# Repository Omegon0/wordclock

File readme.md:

# Quarter Past Five

This is a small 16x16 word clock that can tell the time with a minute resolution. It uses a Xiao RP2040 with four daisy-chained MAX7219 as the display with four key switches to set the time. Breakout pins for connecting a DS3231 RTC are included as well. Has a photoresistor for automatic light adjustment.

### Why?

Because reading the time in words gives me a sense of urgency that reading numbers does not. It makes me get things done more effectively. 

### Building instructions

Obtain parts labeled in the BOM. See either the table below. 

| Component     | Identifier     | Price    | Amazon link |
|---------------|----------------|----------|-------------|
| Xiao RP2040   | XIAO-RP2040    | $9.99    | [Amazon](https://www.amazon.com/Microcontroller-Dual-Core-MicroPython-CircuitPython-Interfaces/dp/B09NNVNW7M/)|
| DS3231        | RTC            | $12.99   | [Amazon](https://www.amazon.com/HiLetgo-AT24C32-Arduino-Without-Battery/dp/B00LX3V7F0/)|
| Switches      | switches       | $10.99*4 | [Amazon](https://www.amazon.com/Mciepny-Waterproof-Dustproof-Pre-Lubricated-Mechanical/dp/B0FF9MBBDR?th=1)|
| MAX7219       | led-matrix     | $8.28    | [Amazon](https://www.amazon.com/3PCS-MAX7219-Matrix-Display-Module/dp/B0FB99TY1Z/)|
| Photoresistor | photoresistor  | $7.39    | [Amazon](https://www.amazon.com/HiLetgo-Dependent-Photoresistor-Photoconductive-Resistance/dp/B00N1ZJUN4/)|
| CR2032        | N/A(separate)  | $3.97    | [Amazon](https://www.amazon.com/Amazon-Basics-CR2032-Compatible-Mercury-Free/dp/B0787K2XWZ/)|

Solder each component into the PCB accordingly, or follow the schematic to wire the pieces together. If using the PCB, make sure that things go the right direction. When soldering the MAX7219, solder the board with the LEDs first and then solder that to the PCB, not the other way around. It's a lot easier.

### Images

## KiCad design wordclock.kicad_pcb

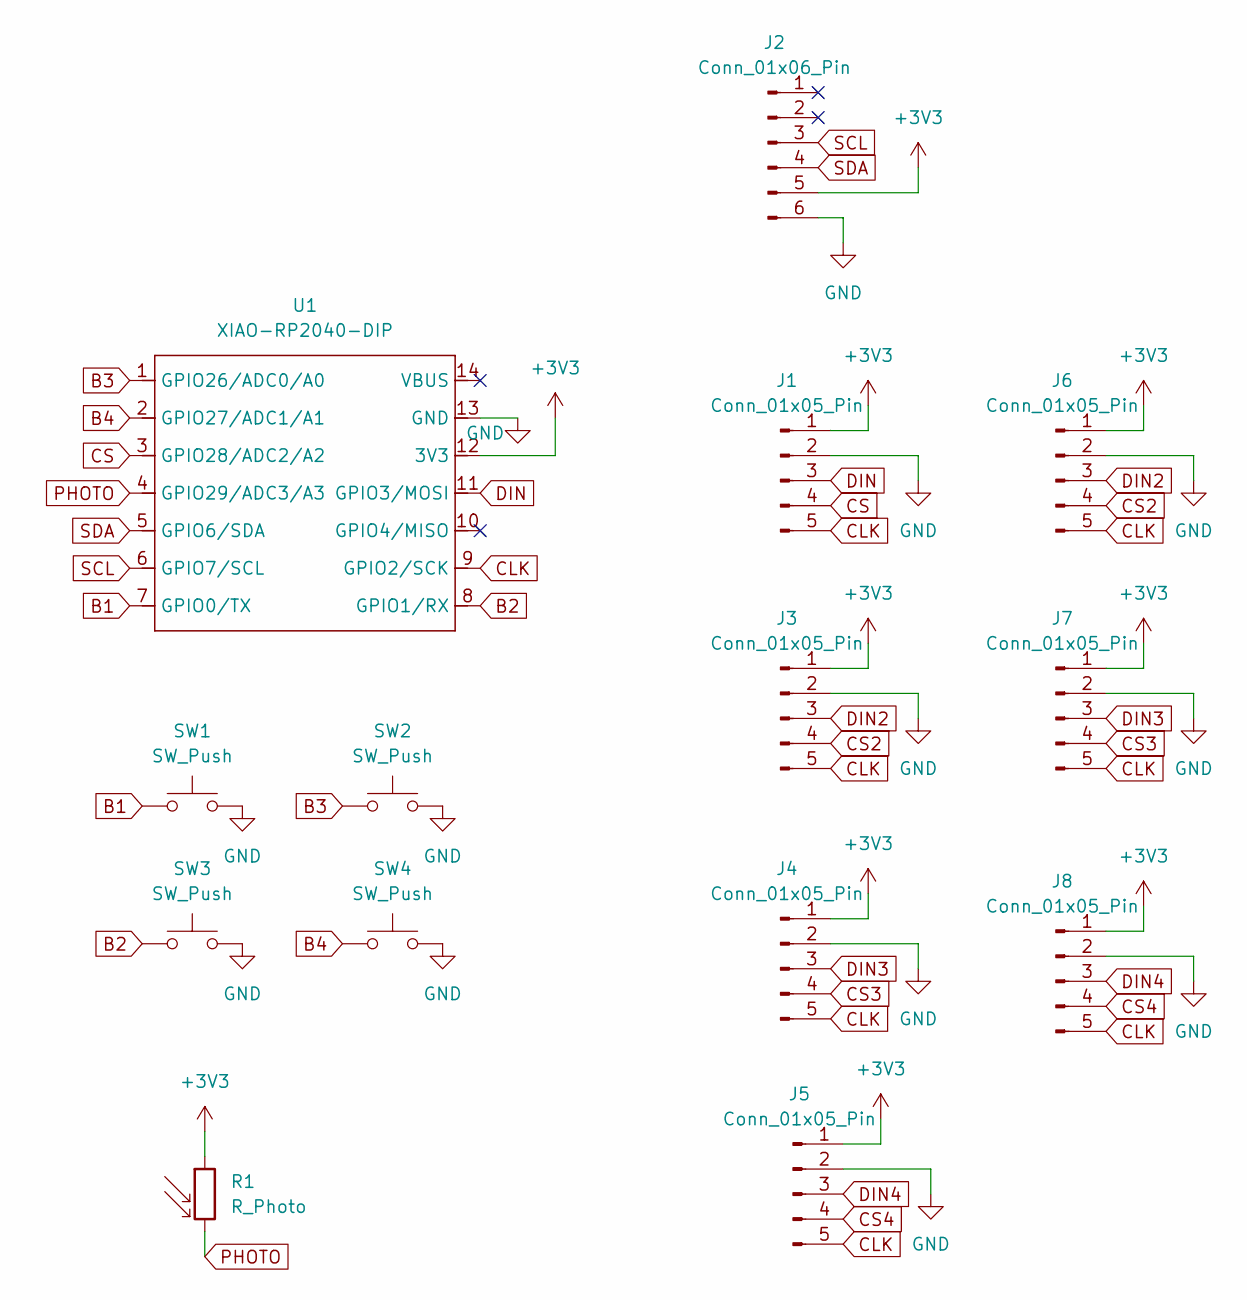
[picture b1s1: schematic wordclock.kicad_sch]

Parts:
J1, J3, J4, J5, J6, J7, J8: Conn_01x05_Pin; PinHeader_1x05_P2.54mm_Vertical
J2: Conn_01x06_Pin; PinHeader_1x06_P2.54mm_Vertical
R1: R_Photo; R_Axial_DIN0204_L3.6mm_D1.6mm_P1.90mm_Vertical
SW1, SW2, SW3, SW4: SW_Push; SW_Cherry_MX_1.00u_PCB
U1: XIAO-RP2040-DIP

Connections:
+3V3: J1.1, J2.5, J3.1, J4.1, J5.1, J6.1, J7.1, J8.1, R1.1, U1.12 (3V3)
B1: SW1.1, U1.7 (GPIO0/TX)
B2: SW3.1, U1.8 (GPIO1/RX)
B3: SW2.1, U1.1 (GPIO26/ADC0/A0)
B4: SW4.1, U1.2 (GPIO27/ADC1/A1)
CLK: J1.5, J3.5, J4.5, J5.5, J6.5, J7.5, J8.5, U1.9 (GPIO2/SCK)
CS: J1.4, U1.3 (GPIO28/ADC2/A2)
CS2: J3.4, J6.4
CS3: J4.4, J7.4
CS4: J5.4, J8.4
DIN: J1.3, U1.11 (GPIO3/MOSI)
DIN2: J3.3, J6.3
DIN3: J4.3, J7.3
DIN4: J5.3, J8.3
GND: J1.2, J2.6, J3.2, J4.2, J5.2, J6.2, J7.2, J8.2, SW1.2, SW2.2, SW3.2, SW4.2, U1.13 (GND)
PHOTO: R1.2, U1.4 (GPIO29/ADC3/A3)
SCL: J2.3, U1.6 (GPIO7/SCL)
SDA: J2.4, U1.5 (GPIO6/SDA)

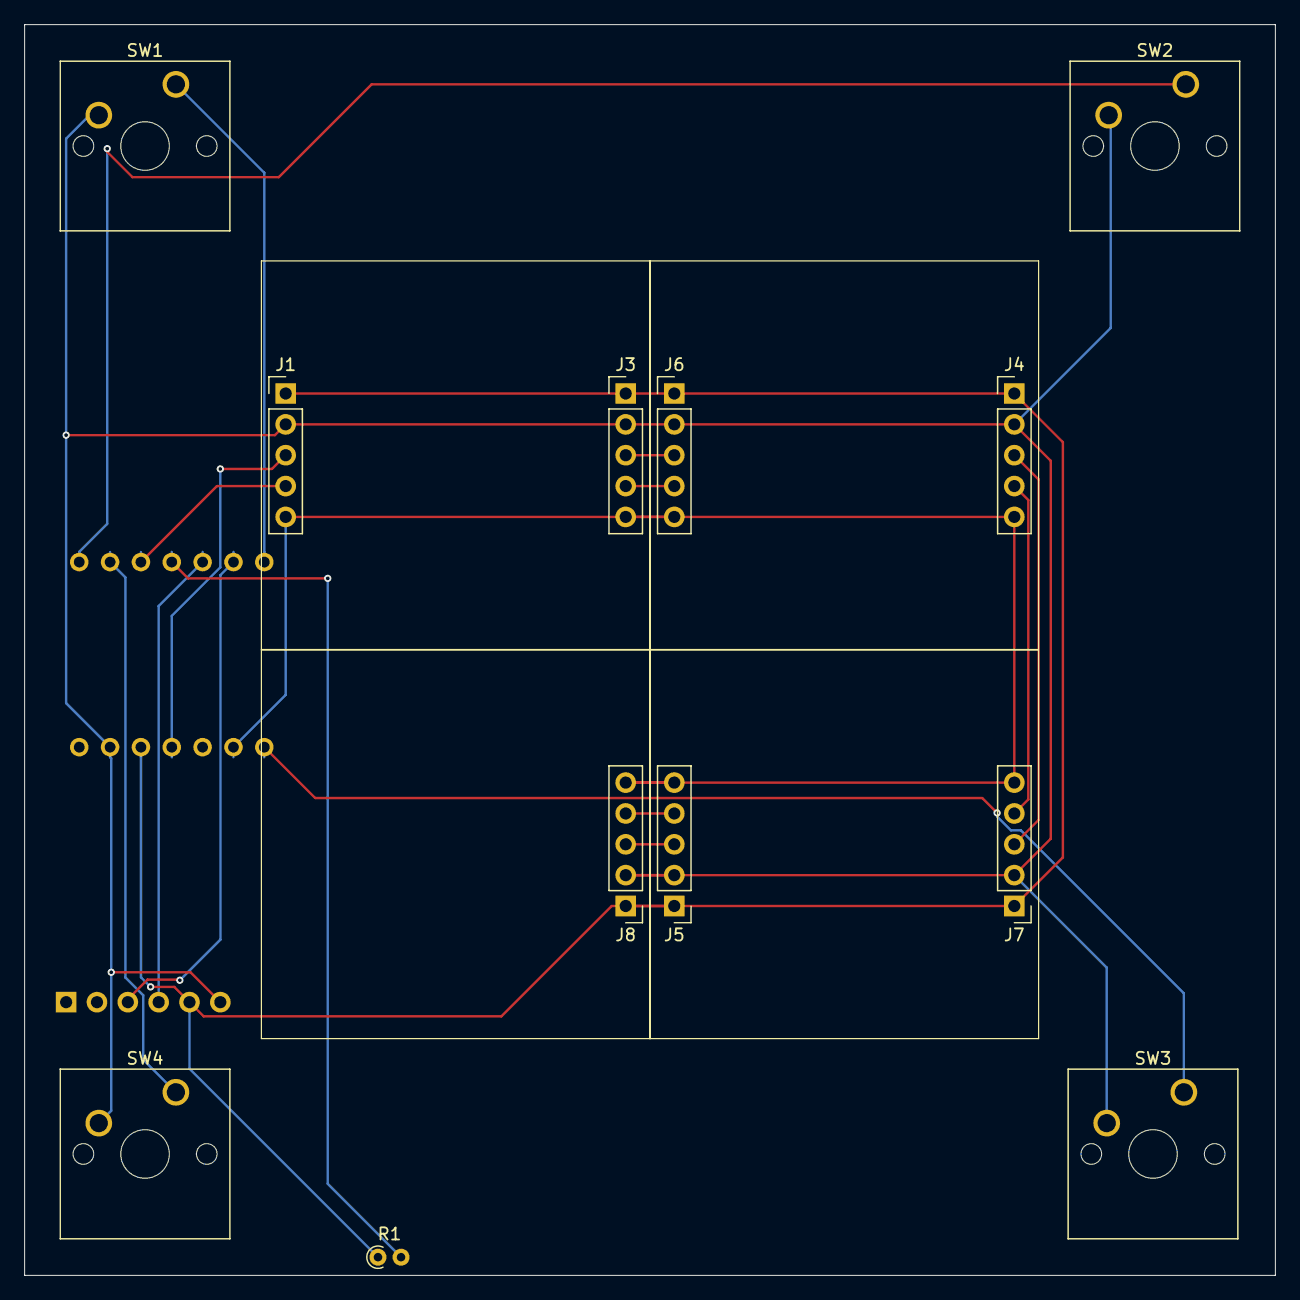
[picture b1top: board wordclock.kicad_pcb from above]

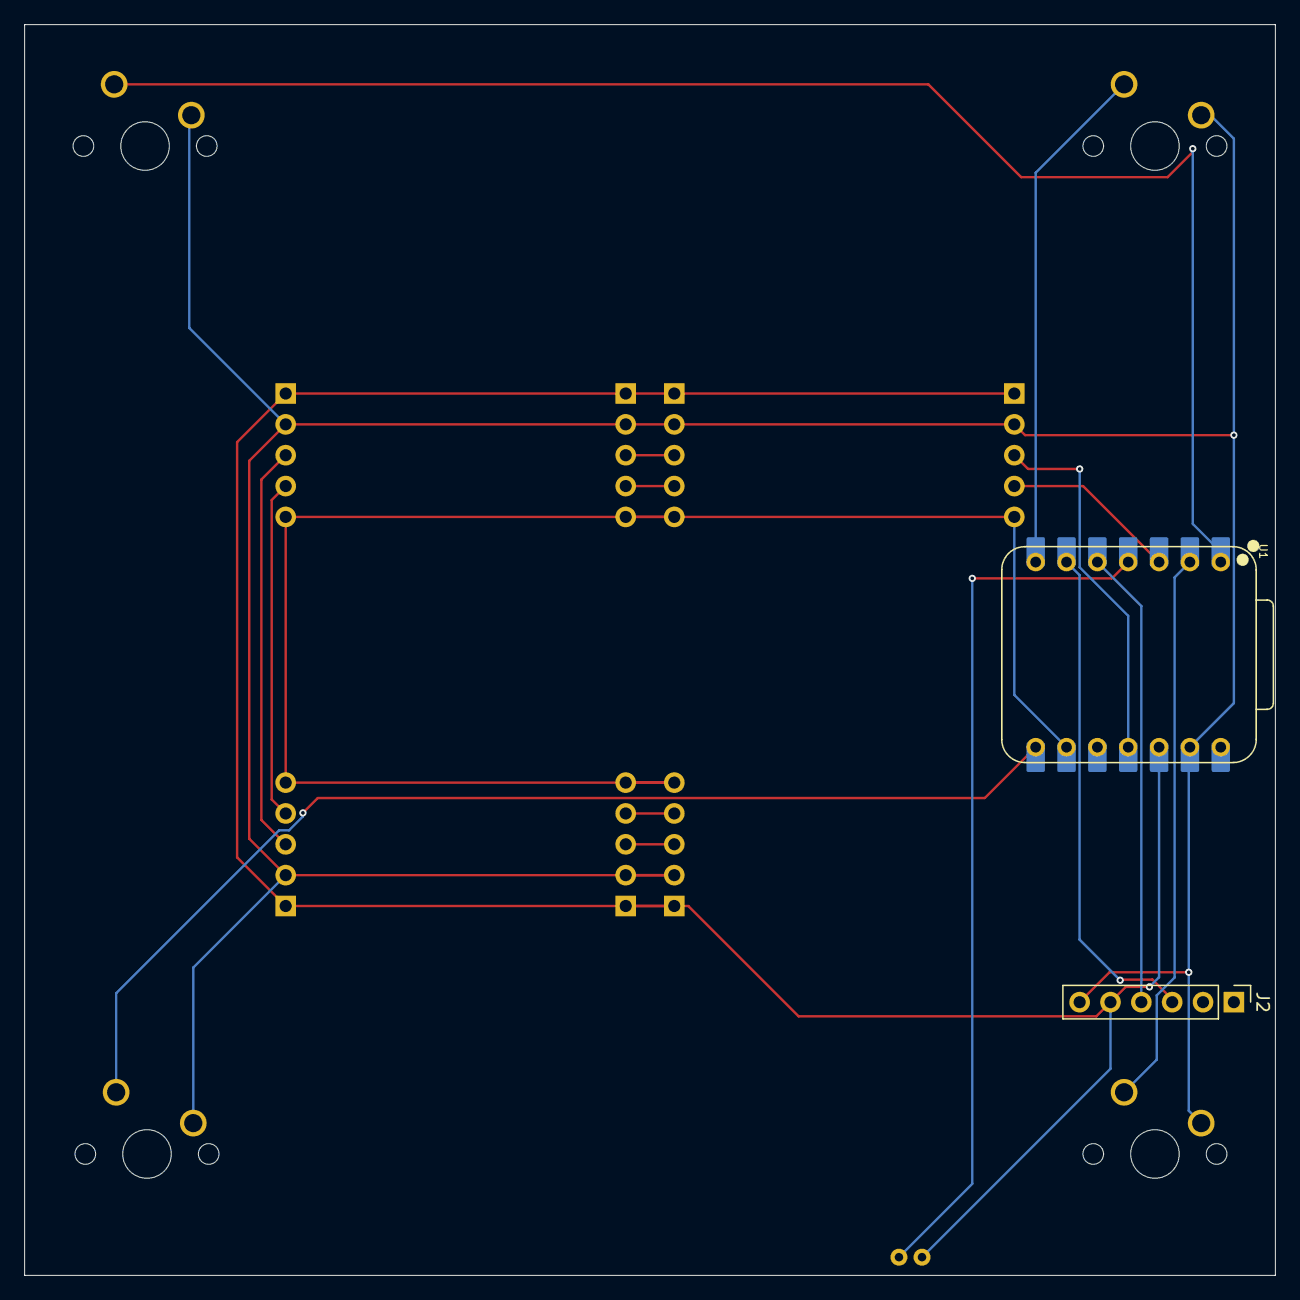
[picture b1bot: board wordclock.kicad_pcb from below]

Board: 2 copper layers, 103.0 x 103.0 mm, 14 parts (2 on the bottom side), 18 nets.

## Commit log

2025-08-31 added readme and journal
2025-08-31 reorganized files
2025-08-31 updated journal
